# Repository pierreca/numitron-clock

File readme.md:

# Simple numitron tubes clock using 595 shift registers.

## Hardware

- TPIC6B595 [Datasheet](https://www.ti.com/lit/ds/symlink/tpic6b595.pdf)
- Numitron Tubes [Info](http://www.tube-tester.com/sites/nixie/data/IV-9/iv-9.htm) [Amazon](https://www.amazon.com/gp/product/B071W9GNP6/)

## References
- [Hackaday Tutorial](https://hackaday.com/2011/12/21/numitron-tube-tutorial/)
- [IV-9 Footprint](https://github.com/andete/ym2413/blob/master/tool/kicad/jyd.pretty/NUM_IV-9.kicad_mod)

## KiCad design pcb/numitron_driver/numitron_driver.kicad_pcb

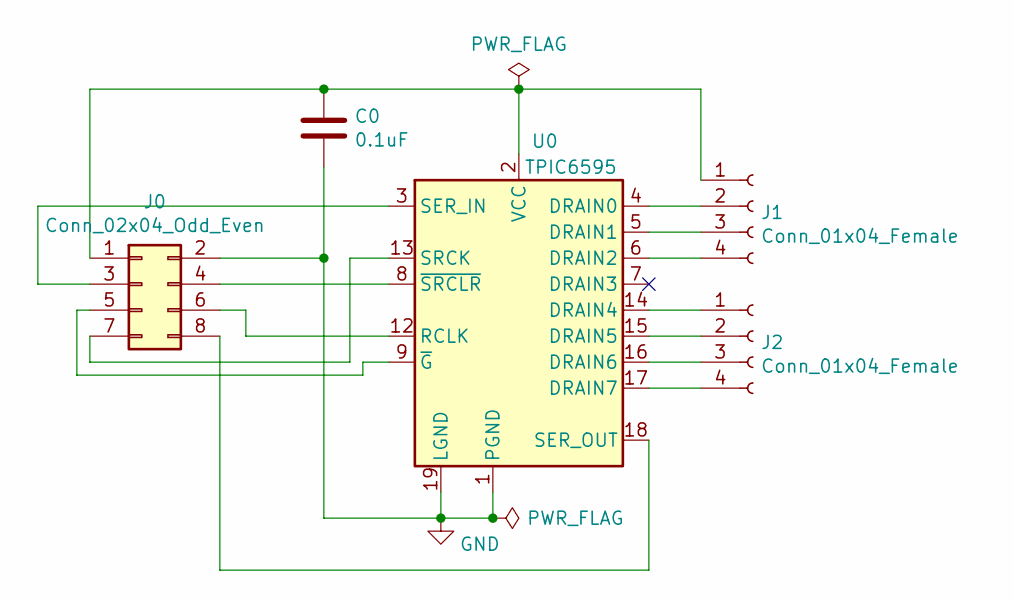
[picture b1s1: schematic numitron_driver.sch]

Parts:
C0: 0.1uF; C_0805_2012Metric_Pad1.15x1.40mm_HandSolder
J0: Conn_02x04_Odd_Even; PinSocket_2x04_P2.54mm_Vertical
J1, J2: Conn_01x04_Female; PinHeader_1x04_P2.54mm_Vertical
U0: TPIC6595; SOIC-20W_7.5x12.8mm_P1.27mm

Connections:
GND: C0.2, J0.2, U0.1 (PGND), U0.10 (PGND), U0.11 (PGND), U0.19 (LGND), U0.20 (PGND)
unnamed: C0.1, J0.1, J1.1, U0.2 (VCC)
unnamed: J0.3, U0.3 (SER_IN)
unnamed: J0.4, U0.8 (~SRCLR)
unnamed: J0.5, U0.9 (~G)
unnamed: J0.6, U0.12 (RCLK)
unnamed: J0.7, U0.13 (SRCK)
unnamed: J0.8, U0.18 (SER_OUT)
unnamed: J1.2, U0.4 (DRAIN0)
unnamed: J1.3, U0.5 (DRAIN1)
unnamed: J1.4, U0.6 (DRAIN2)
unnamed: J2.1, U0.14 (DRAIN4)
unnamed: J2.2, U0.15 (DRAIN5)
unnamed: J2.3, U0.16 (DRAIN6)
unnamed: J2.4, U0.17 (DRAIN7)

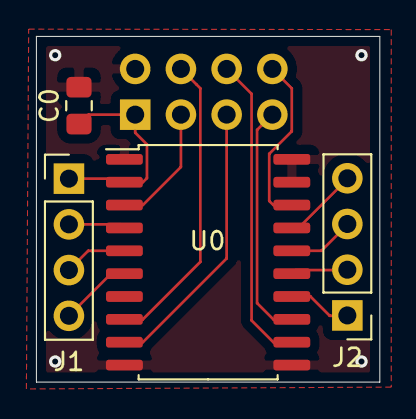
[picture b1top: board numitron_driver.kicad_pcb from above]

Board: 2 copper layers, 19.1 x 19.2 mm, 5 parts (1 on the bottom side), 15 nets.

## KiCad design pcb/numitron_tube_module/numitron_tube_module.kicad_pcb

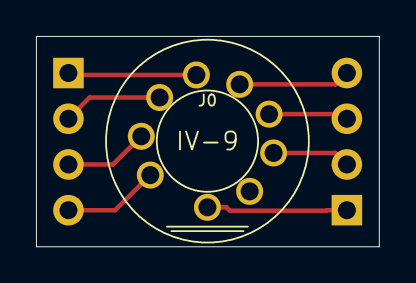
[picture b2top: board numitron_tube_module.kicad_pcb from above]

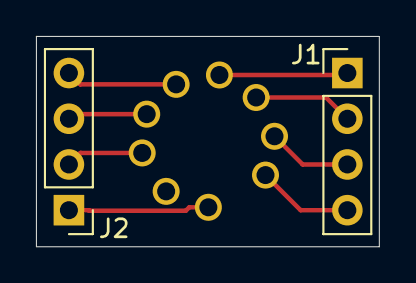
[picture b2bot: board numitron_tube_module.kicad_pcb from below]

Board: 2 copper layers, 19.0 x 11.7 mm, 3 parts (2 on the bottom side), 8 nets.

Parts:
J0: Conn_01x09_Female; NUM_IV-9
J1, J2: Conn_01x04_Male; PinHeader_1x04_P2.54mm_Vertical

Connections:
unnamed: J0.1, J2.1
unnamed: J0.3, J2.2
unnamed: J0.4, J2.3
unnamed: J0.5, J2.4
unnamed: J0.6, J1.1
unnamed: J0.7, J1.2
unnamed: J0.8, J1.3
unnamed: J0.9, J1.4

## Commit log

2019-09-26 Initial readme and early schematics for the numitron driver board
2019-09-26 add .gitignore file
2019-10-10 driver v1.0
2020-04-26 add schematics for whole clock
2020-04-26 not getting anywhere yet
2020-05-06 driver and basic shiftout test code for the tube driver
